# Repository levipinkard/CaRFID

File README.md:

# CaRFID
Custom RFID-based ignition switch replacement, meant for implant use.

FrontPanel.stl is designed for a 2004-2008 Pontiac Grand Prix, but there are several other GM vehicles from this period with the same design for radio mounts.

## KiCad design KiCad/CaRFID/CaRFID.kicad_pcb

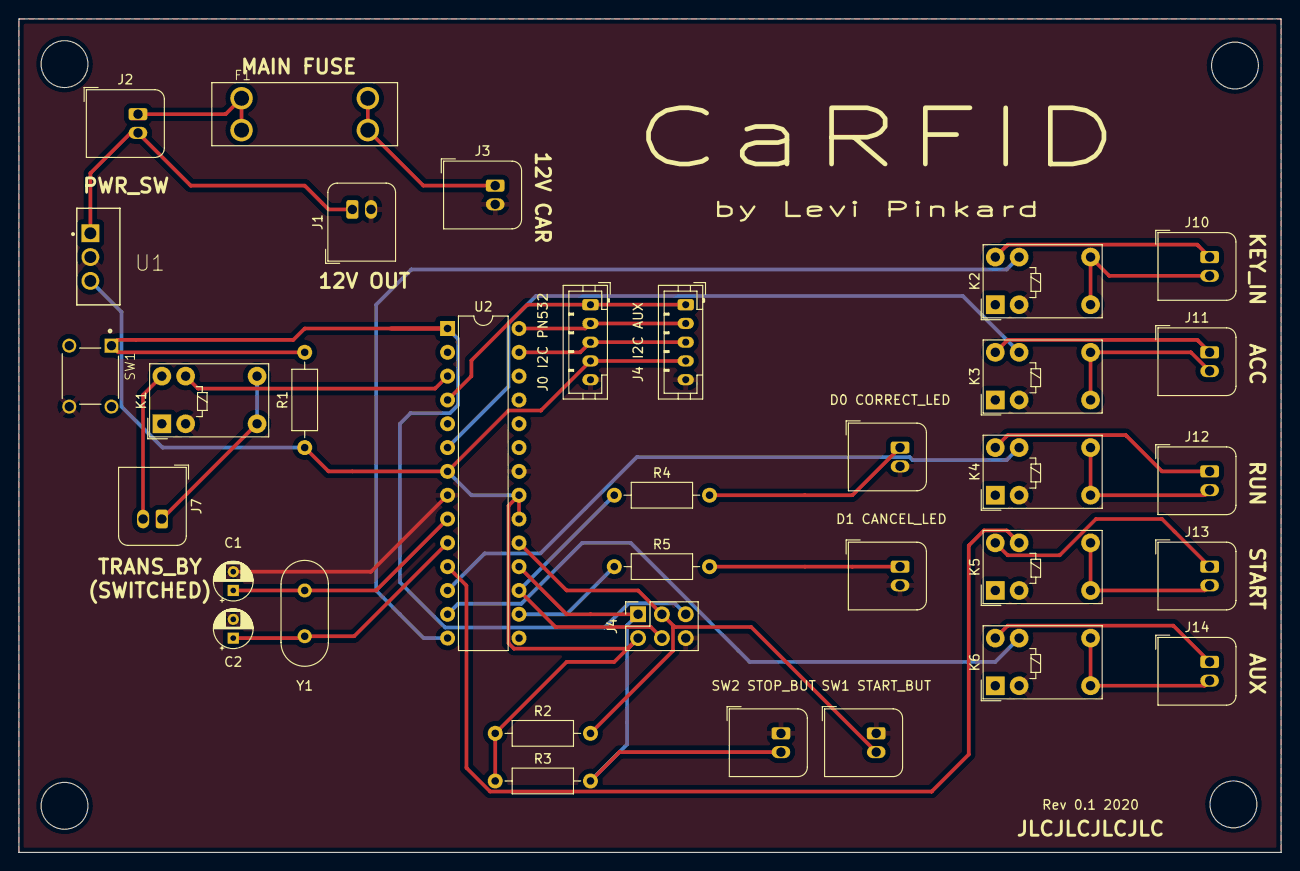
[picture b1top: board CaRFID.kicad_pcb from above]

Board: 2 copper layers, 134.6 x 88.9 mm, 34 parts (0 on the bottom side), 35 nets.

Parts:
C1, C2: 20pF; CP_Radial_D4.0mm_P2.00mm
D1, D2: LED; JST_JWPF_B02B-JWPF-SK-R_1x02_P2.00mm_Vertical
F1: Fuse 5A; FUSE_3557-2
J1, J10, J11, J12, J13, J14: Conn_01x02; JST_JWPF_B02B-JWPF-SK-R_1x02_P2.00mm_Vertical
J2, J3, J7, J8, J9: SW_SPST; JST_JWPF_B02B-JWPF-SK-R_1x02_P2.00mm_Vertical
J4: AVR-ISP-6; PinSocket_2x03_P2.54mm_Vertical
J5, J6: Conn_01x05; JST_PH_B5B-PH-K_1x05_P2.00mm_Vertical
K1, K2, K3, K4, K5, K6: G5V-1; Relay_SPDT_Omron_G5V-1
R1, R2, R3: 1K; R_Axial_DIN0207_L6.3mm_D2.5mm_P10.16mm_Horizontal
R4, R5: 330; R_Axial_DIN0207_L6.3mm_D2.5mm_P10.16mm_Horizontal
SW1: RESET; SW_2-1825910-7
U1: L7805ACV; TO254P460X1020X1945-3P
U2: ATmega328-P; DIP-28_W7.62mm
Y1: 16MHz; Crystal_HC49-U_Vertical

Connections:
+12V: F1.3, F1.4, J3.1
GND: C1.2, C2.2, D1.2, D2.2, J1.2, J3.2, J4.6 (GND), J5.5, J6.5, J8.1, J9.1, K1.2, K2.2, K3.2, K4.2, K5.2, K6.2, SW1.4, U1.2 (GND), U2.8 (GND), U2.22 (GND)
unnamed: C1.1, U2.9 (XTAL1/PB6), Y1.1
unnamed: C2.1, U2.10 (XTAL2/PB7), Y1.2
unnamed: D1.1, R4.2
unnamed: D2.1, R5.2
unnamed: F1.1, F1.2, J2.1
unnamed: J1.1, J2.2, U1.1 (IN)
unnamed: J4.1 (MISO), J9.2, R3.2, U2.18 (PB4)
unnamed: J4.2 (VCC), J5.4, J6.4, R1.1, R2.1, R3.1, U1.3 (OUT), U2.7 (VCC), U2.20 (AVCC), U2.21 (AREF)
unnamed: J4.3 (SCK), J8.2, R2.2, U2.19 (PB5)
unnamed: J4.4 (MOSI), R4.1, U2.17 (PB3)
unnamed: J4.5 (~RST), R1.2, SW1.1, U2.1 (~RESET~/PC6)
unnamed: J5.1, J6.1, U2.4 (PD2)
unnamed: J5.2, J6.2, U2.28 (PC5)
unnamed: J5.3, J6.3, U2.27 (PC4)
unnamed: J7.1, K1.5, K1.6
unnamed: J7.2, K1.10
unnamed: J10.1, K2.10
unnamed: J10.2, K2.5, K2.6
unnamed: J11.1, K3.10
unnamed: J11.2, K3.5, K3.6
unnamed: J12.1, K4.10
unnamed: J12.2, K4.5, K4.6
unnamed: J13.1, K5.10
unnamed: J13.2, K5.5, K5.6
unnamed: J14.1, K6.10
unnamed: J14.2, K6.5, K6.6
unnamed: K1.9, U2.3 (PD1)
unnamed: K2.9, U2.14 (PB0)
unnamed: K3.9, U2.6 (PD4)
unnamed: K4.9, U2.12 (PD6)
unnamed: K5.9, U2.11 (PD5)
unnamed: K6.9, U2.13 (PD7)
unnamed: R5.1, U2.16 (PB2)

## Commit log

2021-01-07 Initial commit to add files
